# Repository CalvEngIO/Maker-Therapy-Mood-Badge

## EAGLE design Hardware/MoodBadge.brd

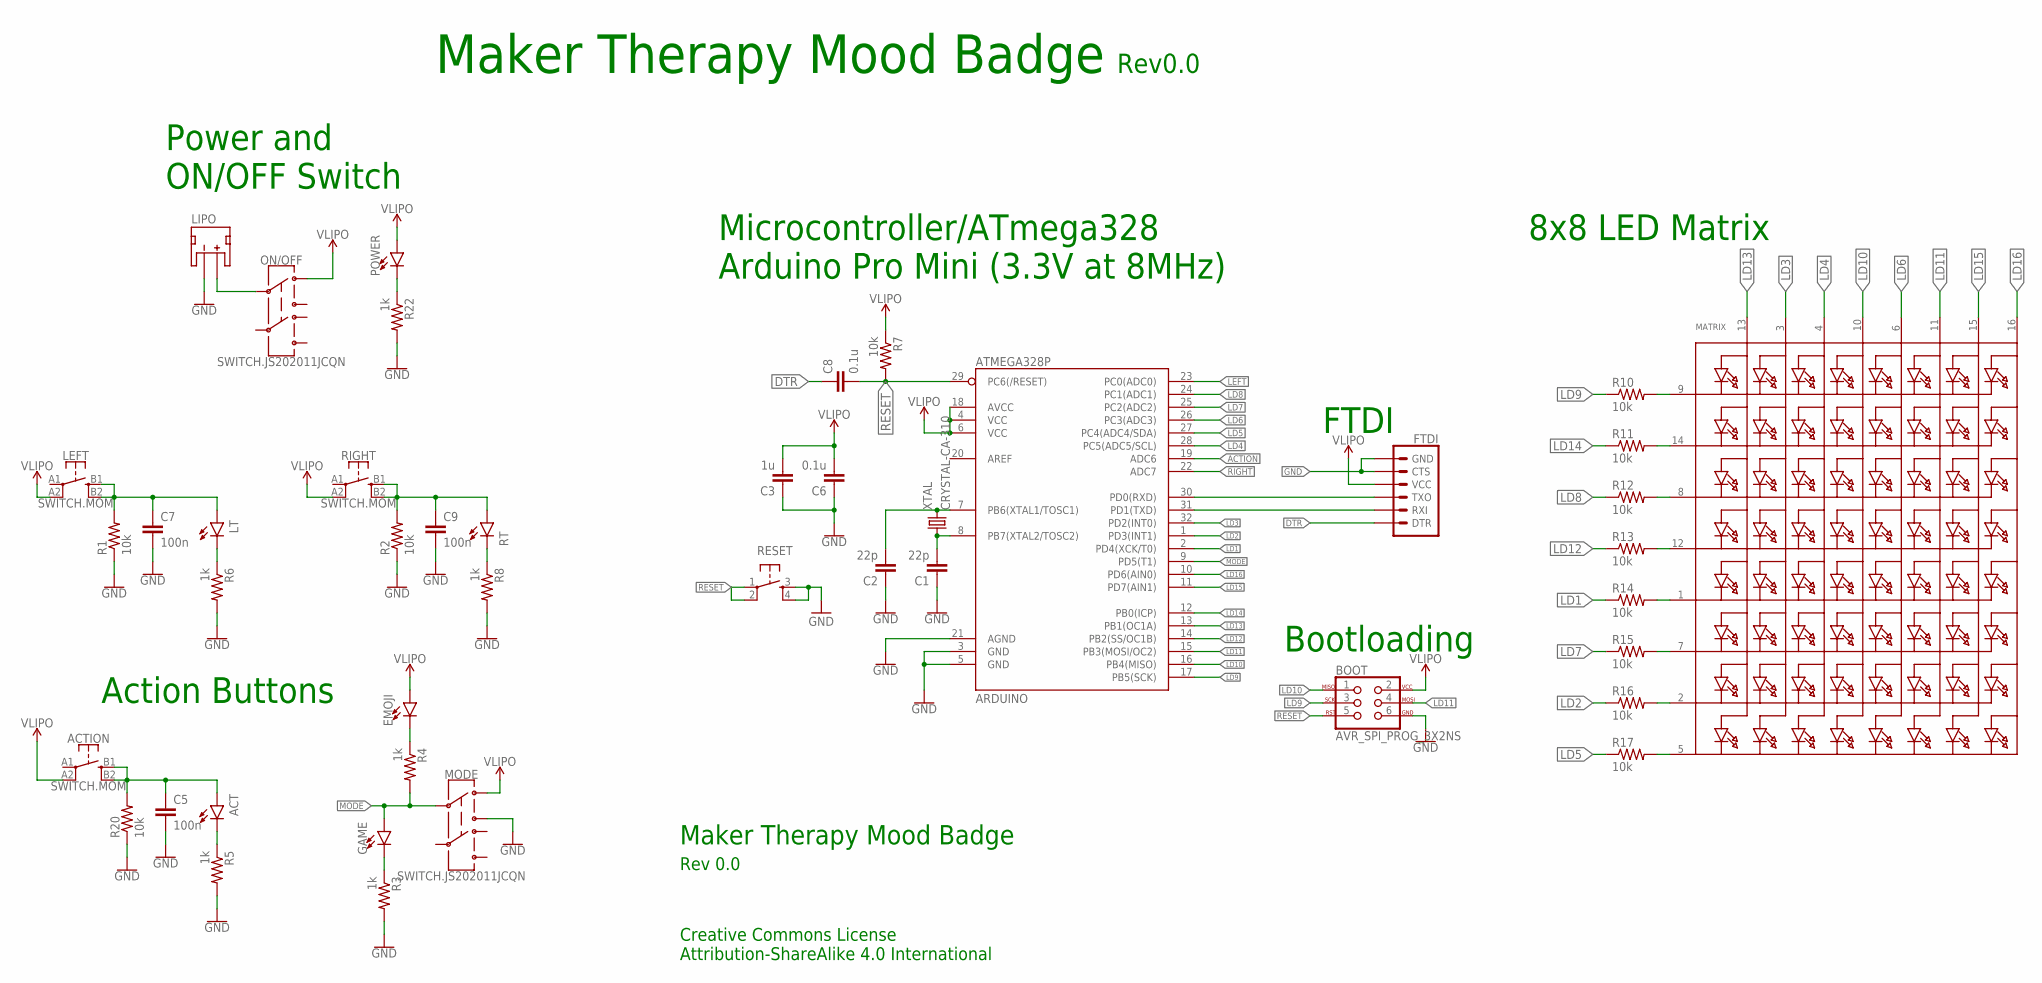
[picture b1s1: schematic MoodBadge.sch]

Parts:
ACT: LED0603; LED-0603
ACTION: SWITCH.MOM; TACTILE_SWITCH_SMD_6.2MM_TALL
ARDUINO: ATMEGA328P; TQFP32-08
BOOT: AVR_SPI_PROG_3X2NS; 2X3-NS
C1, C2: 22p; C0402
C3: 1u; C0402
C5, C7, C9: 100n; C0402
C6, C8: 0.1u; C0402
EMOJI: LED0603; LED-0603
FTDI: 6_PIN_SERIAL_TARGETSILK; 6_PIN_SERIAL_TARGET_SIDE_W_SILK
GAME: LED0603; LED-0603
LEFT: SWITCH.MOM; TACTILE_SWITCH_SMD_6.2MM_TALL
LIPO: JST_2MM_MALE; JST-2-SMD
LT: LED0603; LED-0603
MATRIX: SEGMENT_8X8_ROWCATHODEM12A881UR; SEGMENT_BL-M12A881UR
MODE: SWITCH.JS202011JCQN; SWITCH.00
ON/OFF: SWITCH.JS202011JCQN; SWITCH.00
POWER: LED5MM; LED_5MM
R1, R2, R7, R10, R11, R12, R13, R14, R15, R16, R17, R20: 10k; R0402
R3, R4, R5, R6, R8, R22: 1k; R0402
RESET: BUTTON-PTS830GG140; BUTTON-GULLWING
RIGHT: SWITCH.MOM; TACTILE_SWITCH_SMD_6.2MM_TALL
RT: LED0603; LED-0603
U$8: CALVENGIO_HANDLEHANDLE.05; CALVENGIO_HANDLE.05
U$10: MAKERTHERAPY.HANDLEMAKERTHERAPY.HANDLE.175; MAKERTHERAPY.HANDLE.175
XTAL: CRYSTAL-CA-310; CA-301

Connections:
ACTION: ACT.A, ACTION.B1 (3), ACTION.B2 (4), ARDUINO.19 (ADC6), C5.1, R20.2
DTR: C8.1, FTDI.P$1 (DTR)
GND: ARDUINO.3 (GND), ARDUINO.5 (GND), ARDUINO.21 (AGND), BOOT.6, C1.1, C2.1, C3.1, C5.2, C6.1, C7.2, C9.2, FTDI.P$5 (CTS), FTDI.P$6 (GND), LIPO.1 (-), MODE.3, R1.1, R2.1, R3.2, R5.2, R6.2, R8.2, R20.1, R22.2, RESET.3, RESET.4
LD1: ARDUINO.2 (PD4(XCK/T0)), R14.1
LD2: ARDUINO.1 (PD3(INT1)), R16.1
LD3: ARDUINO.32 (PD2(INT0)), MATRIX.3 (A2)
LD4: ARDUINO.28 (PC5(ADC5/SCL)), MATRIX.4 (A3)
LD5: ARDUINO.27 (PC4(ADC4/SDA)), R17.1
LD6: ARDUINO.26 (PC3(ADC3)), MATRIX.6 (A5)
LD7: ARDUINO.25 (PC2(ADC2)), R15.1
LD8: ARDUINO.24 (PC1(ADC1)), R12.1
LD9: ARDUINO.17 (PB5(SCK)), BOOT.3, R10.1
LD10: ARDUINO.16 (PB4(MISO)), BOOT.1, MATRIX.10 (A4)
LD11: ARDUINO.15 (PB3(MOSI/OC2)), BOOT.4, MATRIX.11 (A6)
LD12: ARDUINO.14 (PB2(SS/OC1B)), R13.1
LD13: ARDUINO.13 (PB1(OC1A)), MATRIX.13 (A1)
LD14: ARDUINO.12 (PB0(ICP)), R11.1
LD15: ARDUINO.11 (PD7(AIN1)), MATRIX.15 (A7)
LD16: ARDUINO.10 (PD6(AIN0)), MATRIX.16 (A8)
LEFT: ARDUINO.23 (PC0(ADC0)), C7.1, LEFT.B1 (3), LEFT.B2 (4), LT.A, R1.2
MODE: ARDUINO.9 (PD5(T1)), GAME.A, MODE.2, R4.2
unnamed: ARDUINO.7 (PB6(XTAL1/TOSC1)), C2.2, XTAL.2
unnamed: ARDUINO.8 (PB7(XTAL2/TOSC2)), C1.2, XTAL.1
unnamed: POWER.K (C), R22.1
unnamed: GAME.C, R3.1
unnamed: LIPO.2 (+), ON/OFF.2
unnamed: EMOJI.C, R4.1
unnamed: ACT.C, R5.1
unnamed: LT.C, R6.1
unnamed: R8.1, RT.C
unnamed: MATRIX.9 (K1), R10.2
unnamed: MATRIX.14 (K2), R11.2
unnamed: MATRIX.8 (K3), R12.2
unnamed: MATRIX.12 (K4), R13.2
unnamed: MATRIX.1 (K5), R14.2
unnamed: MATRIX.7 (K6), R15.2
unnamed: MATRIX.2 (K7), R16.2
unnamed: MATRIX.5 (K8), R17.2
RESET: ARDUINO.29 (PC6(/RESET)), BOOT.5, C8.2, R7.2, RESET.1, RESET.2
RIGHT: ARDUINO.22 (ADC7), C9.1, R2.2, RIGHT.B1 (3), RIGHT.B2 (4), RT.A
RXI/FTDI: ARDUINO.31 (PD1(TXD)), FTDI.P$3 (RXI)
TXO/FTDI: ARDUINO.30 (PD0(RXD)), FTDI.P$2 (TXO)
VLIPO: ACTION.A2 (2), ARDUINO.4 (VCC), ARDUINO.6 (VCC), ARDUINO.18 (AVCC), BOOT.2, C3.2, C6.2, EMOJI.A, FTDI.P$4 (VCC), LEFT.A2 (2), MODE.1, ON/OFF.1, POWER.A, R7.1, RIGHT.A2 (2)

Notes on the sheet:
Microcontroller/ATmega328 Arduino Pro Mini (3.3V at 8MHz)
FTDI
Bootloading
8x8 LED Matrix
Power and ON/OFF Switch
Action Buttons
Maker Therapy Mood Badge
Rev 0.0
Creative Commons License Attribution-ShareAlike 4.0 International
Rev0.0

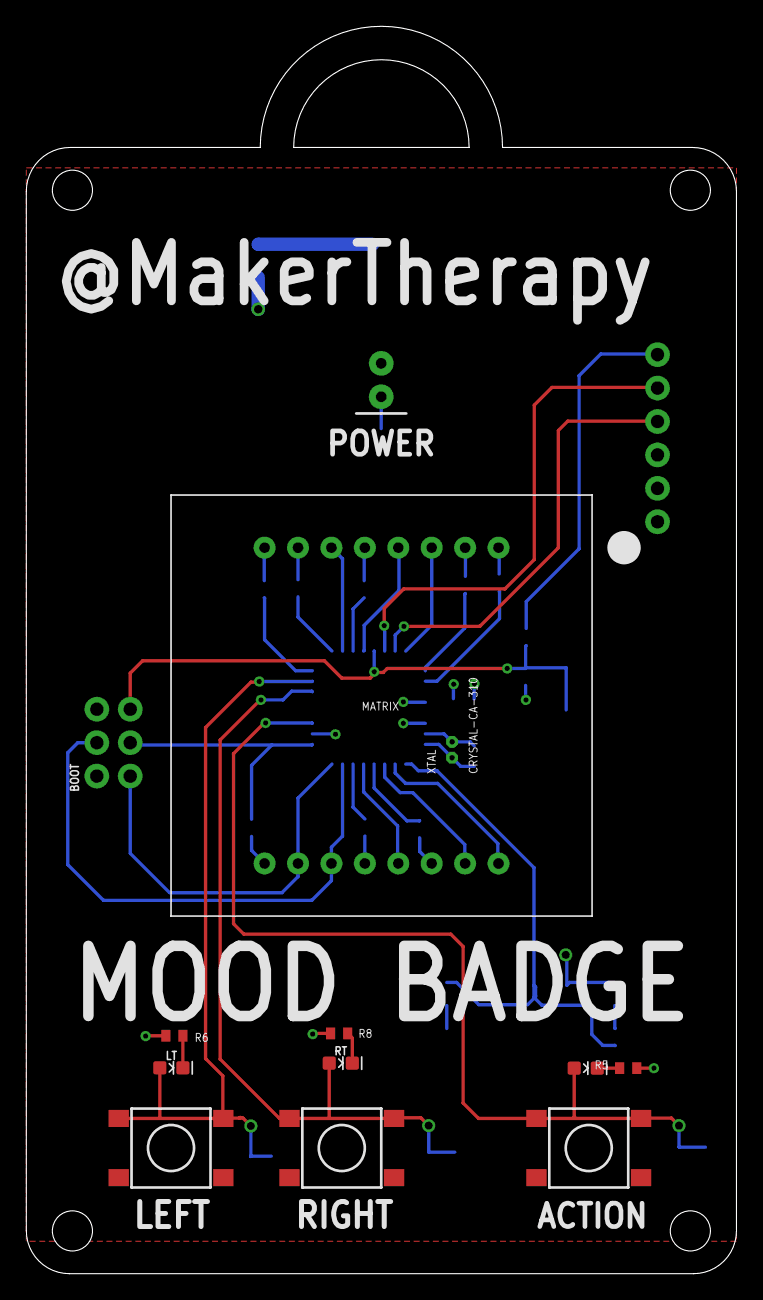
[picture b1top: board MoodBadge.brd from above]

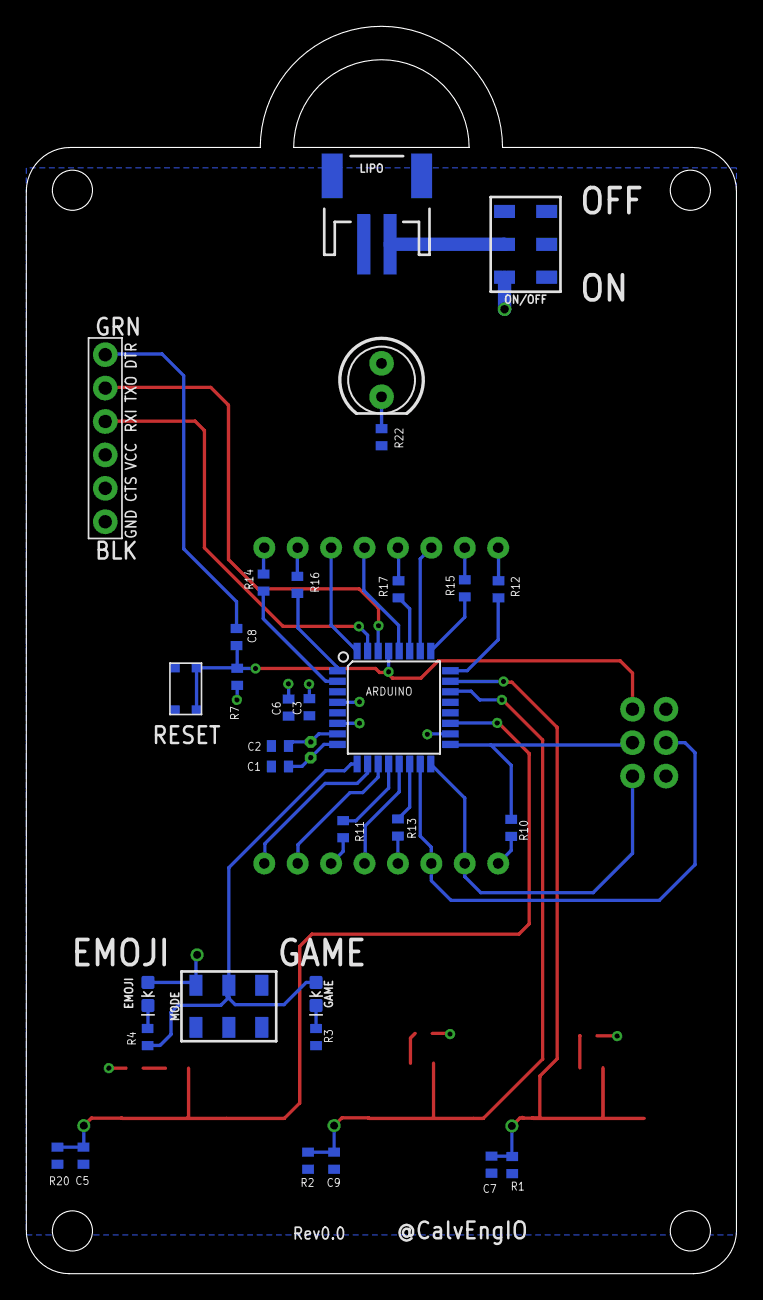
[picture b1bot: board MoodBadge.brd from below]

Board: 2 copper layers, 54.0 x 94.8 mm, 46 parts (33 on the bottom side), 43 nets.

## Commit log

2017-04-13 Create LICENSE-Hardware
2017-04-13 Create LICENSE-Software
2017-04-13 initial commit. Incomplete - work in progress
2017-04-15 first order sent to OSHPark
2017-05-04 updates to the code and movie demo
2017-05-07 new game concept based off Galaga prototype
2017-07-22 Fixed compiler errors
2017-08-05 Added Screen interface and fixed errors
2021-03-06 updated gitignore file

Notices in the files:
parts and their libraries:
SparkFun-DigitalIC: Licensing: Creative Commons ShareAlike 4.0 International - https://creativecommons.org/licenses/by-sa/4.0
